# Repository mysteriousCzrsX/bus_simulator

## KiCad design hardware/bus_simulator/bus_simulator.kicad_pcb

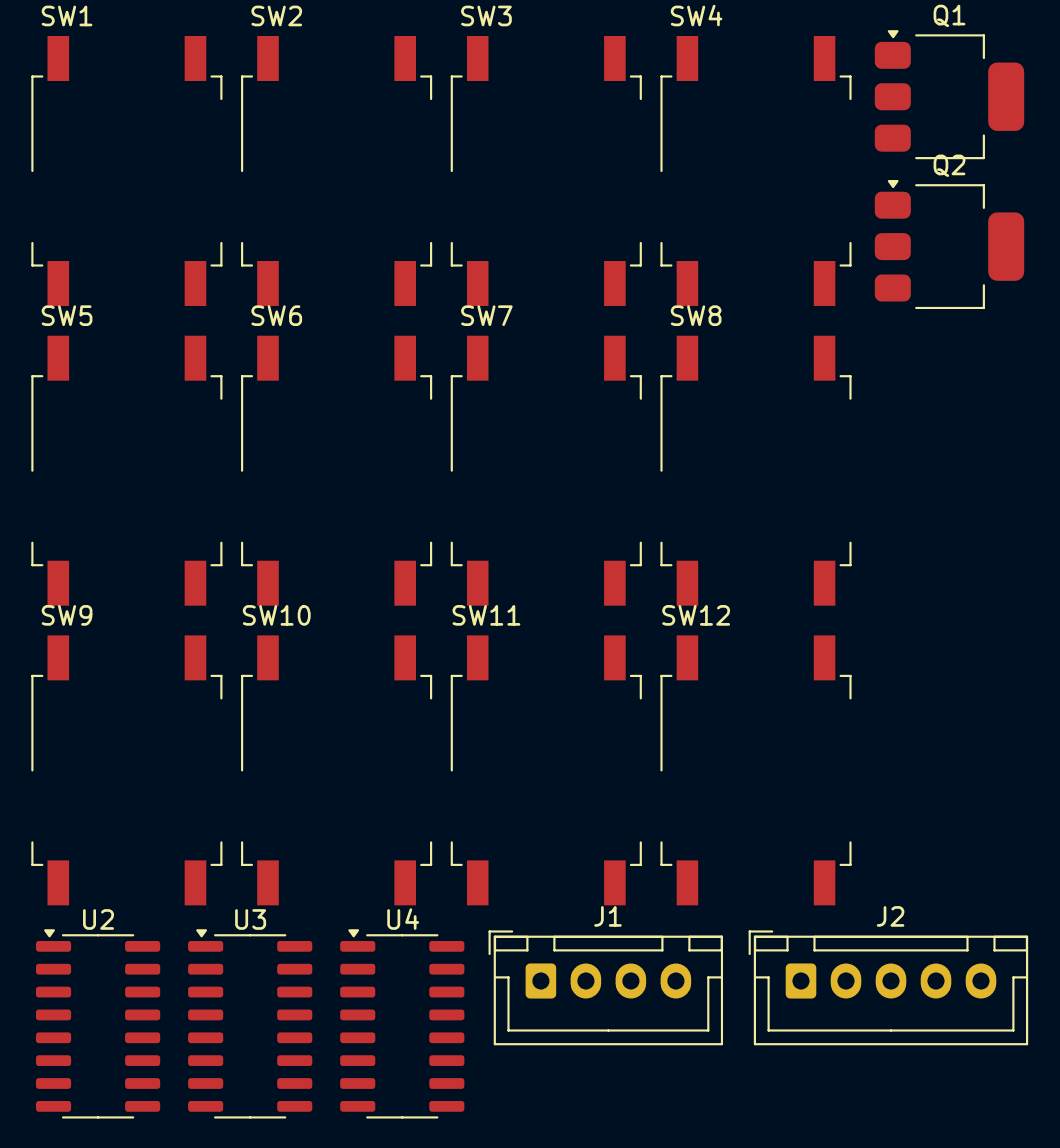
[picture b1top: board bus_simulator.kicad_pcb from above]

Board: 2 copper layers, 19 parts (0 on the bottom side), 8 nets, no tracks yet.

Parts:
J1: I2C_LCD; JST_XH_B4B-XH-A_1x04_P2.50mm_Vertical
J2: Encoder; JST_XH_B5B-XH-A_1x05_P2.50mm_Vertical
Q1, Q2: BUK7880-55A; SOT-223-3_TabPin2
SW1, SW2, SW3, SW4, SW5, SW6, SW7, SW8, SW9, SW10, SW11, SW12: SW_Push; SW_MEC_5GSH9
U2, U3, U4: 74HC595; SOIC-16_3.9x9.9mm_P1.27mm

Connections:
+3.3V: J2.5, Q1.1 (G), Q2.1 (G), U2.10 (~SRCLR), U2.16 (VCC), U3.10 (~SRCLR), U3.16 (VCC), U4.10 (~SRCLR), U4.16 (VCC)
GND: J1.1, J2.1, SW1.1, SW2.1, SW3.1, SW4.1, SW5.1, SW6.1, SW7.1, SW8.1, SW9.1, SW10.1, SW11.1, SW12.1, U2.8 (GND), U2.13 (~OE), U3.8 (GND), U3.13 (~OE), U4.8 (GND), U4.13 (~OE)
unnamed: J1.3, Q1.2 (D)
unnamed: J1.4, Q2.2 (D)
unnamed: U2.11 (SRCLK), U3.11 (SRCLK), U4.11 (SRCLK)
unnamed: U2.12 (RCLK), U3.12 (RCLK), U4.12 (RCLK)
unnamed: U2.9 (QH'), U3.14 (SER)
unnamed: U3.9 (QH'), U4.14 (SER)

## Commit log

2024-03-13 Added folder structure
2024-03-17 Added schematic
2024-03-17 Finished schematic
2024-03-20 Implemented cpu execution logic
2024-03-22 Implemented alu operations
2024-03-24 Added some cpu logic
2024-03-26 Added Io class
2024-05-14 LCD test code
2024-12-08 Changed cpu class name
2024-12-08 Basic menu test
2024-12-08 Implemented menu working menu basics
2024-12-08 Added execution scheduling mechanizm
2024-12-08 add cpu state handling
2024-12-09 bus_cpu.cpp: fix transmiter control decoding sequence
2024-12-10 Added cpu execution control to menu
2024-12-10 Implemented execution speed changing
2024-12-10 Fixed idle task
2024-12-10 Changed led naming
2024-12-10 Added missing alu operations
2024-12-10 Some bugfixin
2024-12-10 Removed debug messages
2025-01-05 Updated gitignore
2025-01-05 Added basic document structure
2025-01-07 Analysys chapter
2025-01-08 Finished analysys chapter
2025-01-08 Add voltage level converter
2025-01-08 Concept chapter progres
2025-01-10 fixed some things
2025-01-12 All the fixes
2025-01-13 Analiza finished
2025-01-13 Implementation progress
2025-01-13 Fixed typos and removed old comments
2025-01-13 More progress on implementation
2025-01-14 Implementation user interface
2025-01-14 Removed redundant checks
2025-01-14 Fixes after reviev
2025-01-14 Tests progress
2025-01-16 Tests chapter
2025-01-16 Fixed typo
2025-01-16 Final fixes
2025-10-20 Schematic fixes
